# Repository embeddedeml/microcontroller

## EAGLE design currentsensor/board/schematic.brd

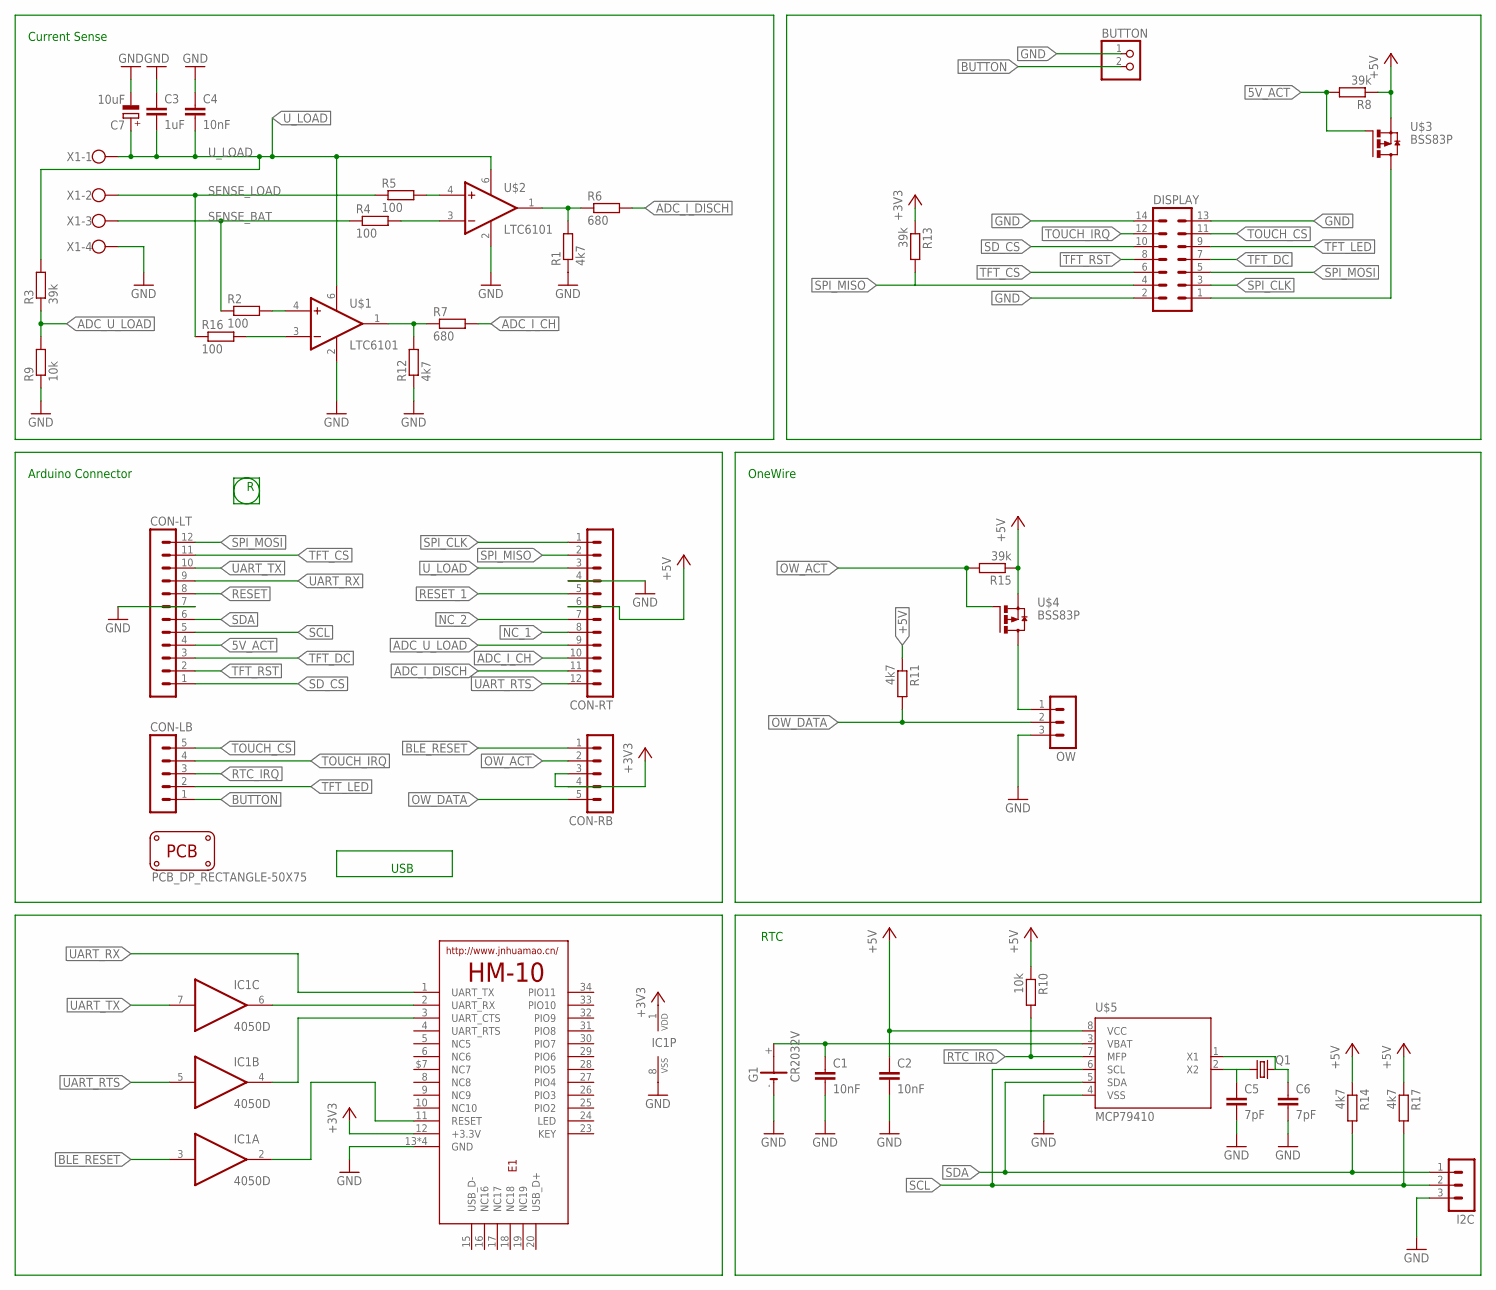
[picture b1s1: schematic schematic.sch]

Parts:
BUTTON: PINHD-1X2; 1X02
C1, C2, C4: 10nF; C1206
C3: 1uF; C1206
C5, C6: 7pF; C1206
C7: 10uF; PANASONIC_B
CON-LB: MA05-1
CON-LT: MA12-1
CON-RB: MA05-1
CON-RT: MA12-1
DISPLAY: MA07-2
E1: HM-10-BOARD; 26.9X13X2.2_BOARD
G1: CR2032V
I2C: MA03-1
IC1: 4050D; SO16
OW: MA03-1
PCB1: PCB_DP_RECTANGLE-50X75; DP5075_V1
Q1: CRYSTALTC26H; TC26H
R1, R11, R12, R14, R17: 4k7; R1206
R2, R4, R5, R16: 100; R1206
R3, R8, R13, R15: 39k; R1206
R6, R7: 680; R1206
R9, R10: 10k; R1206
U$1, U$2: LTC6101; TSOT23-6
U$3, U$4: BSS83P; SOT23
U$5: MCP79410; SOIC8
X1: W237-4

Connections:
5V_ACT: CON-LT.4, R8.2, U$3.1 (G)
+3V3: CON-RB.3, CON-RB.4, E1.12 (+3.3V), IC1.1 (VDD), R13.1
+5V: C2.1, CON-RT.6, R8.1, R10.1, R11.1, R14.1, R15.1, R17.1, U$3.2 (S), U$4.2 (S), U$5.8 (VCC)
ADC_I_CH: CON-RT.10, R7.2
ADC_I_CH_UNPROT: R7.1, R12.2, U$1.1 (OUT1)
ADC_I_DISCH: CON-RT.11, R6.2
ADC_I_DISCH_UNPROT: R1.2, R6.1, U$2.1 (OUT1)
ADC_U_LOAD: CON-RT.9, R3.1, R9.2
BLE_RESET: CON-RB.1, IC1.3 (I)
BUTTON: BUTTON.2, CON-LB.1
GND: BUTTON.1, C1.2, C2.2, C3.1, C4.1, C5.2, C6.2, C7.-, CON-LT.7, CON-RT.4, DISPLAY.2, DISPLAY.13, DISPLAY.14, E1.13 (GND), E1.14 (GND), E1.21 (GND), E1.22 (GND), G1.-, I2C.3, IC1.8 (VSS), OW.3, R1.1, R9.1, R12.1, U$1.2 (V-), U$2.2 (V-), U$5.4 (VSS), X1.4
LCD_5V: DISPLAY.1, U$3.3 (D)
unnamed: R5.2, U$2.4 (+IN)
unnamed: R4.2, U$2.3 (-IN)
unnamed: R2.2, U$1.4 (+IN)
unnamed: R16.2, U$1.3 (-IN)
unnamed: E1.3 (UART_CTS), IC1.4 (O)
unnamed: E1.2 (UART_RX), IC1.6 (O)
unnamed: E1.11 (RESET), IC1.2 (O)
unnamed: OW.1, U$4.3 (D)
unnamed: C5.1, Q1.1, U$5.2 (X2)
unnamed: C6.1, Q1.2, U$5.1 (X1)
NC_1: CON-RT.8
NC_2: CON-RT.7
OW_ACT: CON-RB.2, R15.2, U$4.1 (G)
OW_DATA: CON-RB.5, OW.2, R11.2
RESET: CON-LT.8
RESET_1: CON-RT.5
RTC_IRQ: CON-LB.3, R10.2, U$5.7 (MFP)
SCL: CON-LT.5, I2C.2, R17.2, U$5.6 (SCL)
SDA: CON-LT.6, I2C.1, R14.2, U$5.5 (SDA)
SD_CS: CON-LT.1, DISPLAY.10
SENSE_BAT: R2.1, R4.1, X1.3
SENSE_LOAD: R5.1, R16.1, X1.2
SPI_CLK: CON-RT.1, DISPLAY.3
SPI_MISO: CON-RT.2, DISPLAY.4, R13.2
SPI_MOSI: CON-LT.12, DISPLAY.5
TFT_CS: CON-LT.11, DISPLAY.6
TFT_DC: CON-LT.3, DISPLAY.7
TFT_LED: CON-LB.2, DISPLAY.9
TFT_RST: CON-LT.2, DISPLAY.8
TOUCH_CS: CON-LB.5, DISPLAY.11
TOUCH_IRQ: CON-LB.4, DISPLAY.12
UART_RTS: CON-RT.12, IC1.5 (I)
UART_RX: CON-LT.9, E1.1 (UART_TX)
UART_TX: CON-LT.10, IC1.7 (I)
U_LOAD: C3.2, C4.2, C7.+, CON-RT.3, R3.2, U$1.6 (V+), U$2.6 (V+), X1.1
VBAK: C1.1, G1.+, U$5.3 (VBAT)

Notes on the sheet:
Arduino Connector
Current Sense
USB
OneWire
RTC

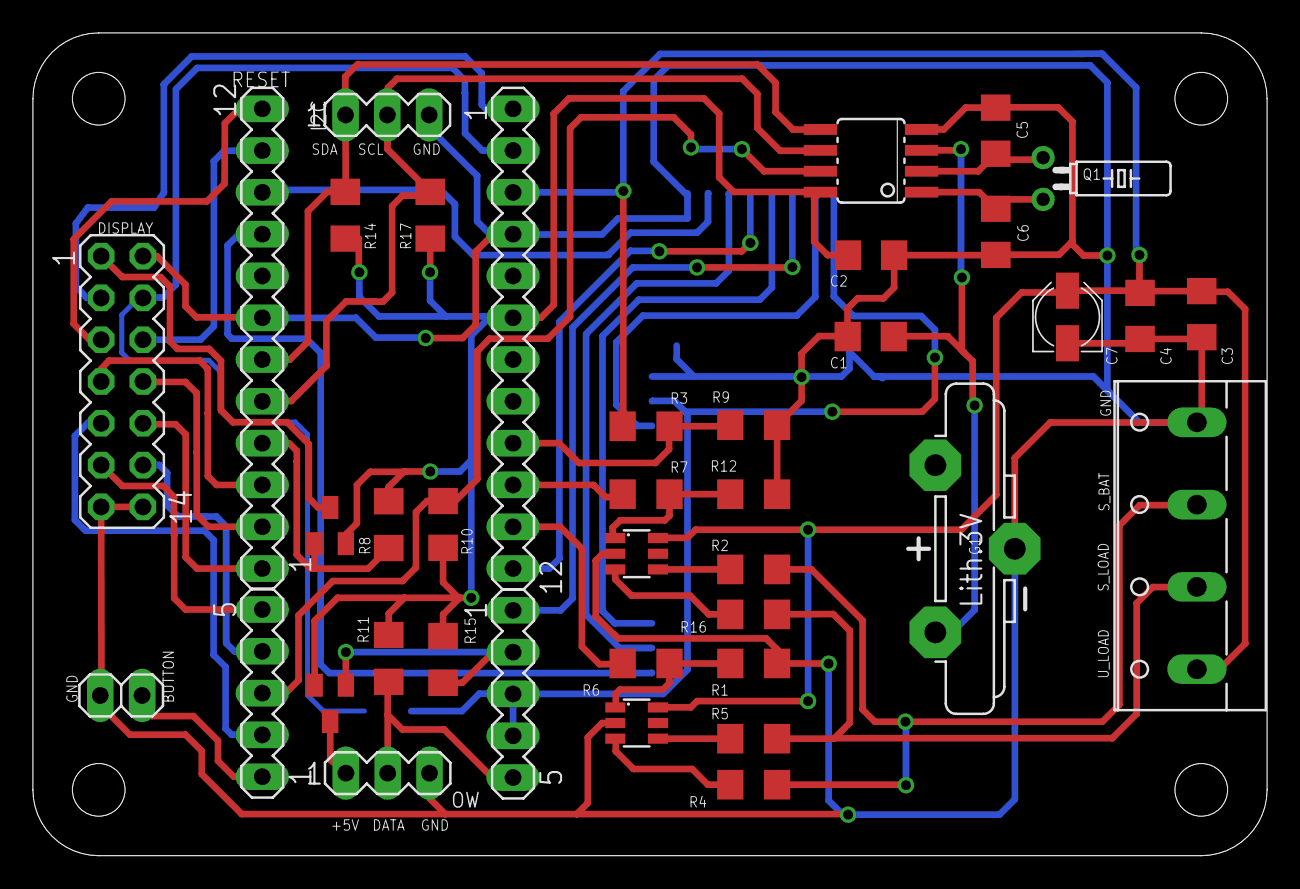
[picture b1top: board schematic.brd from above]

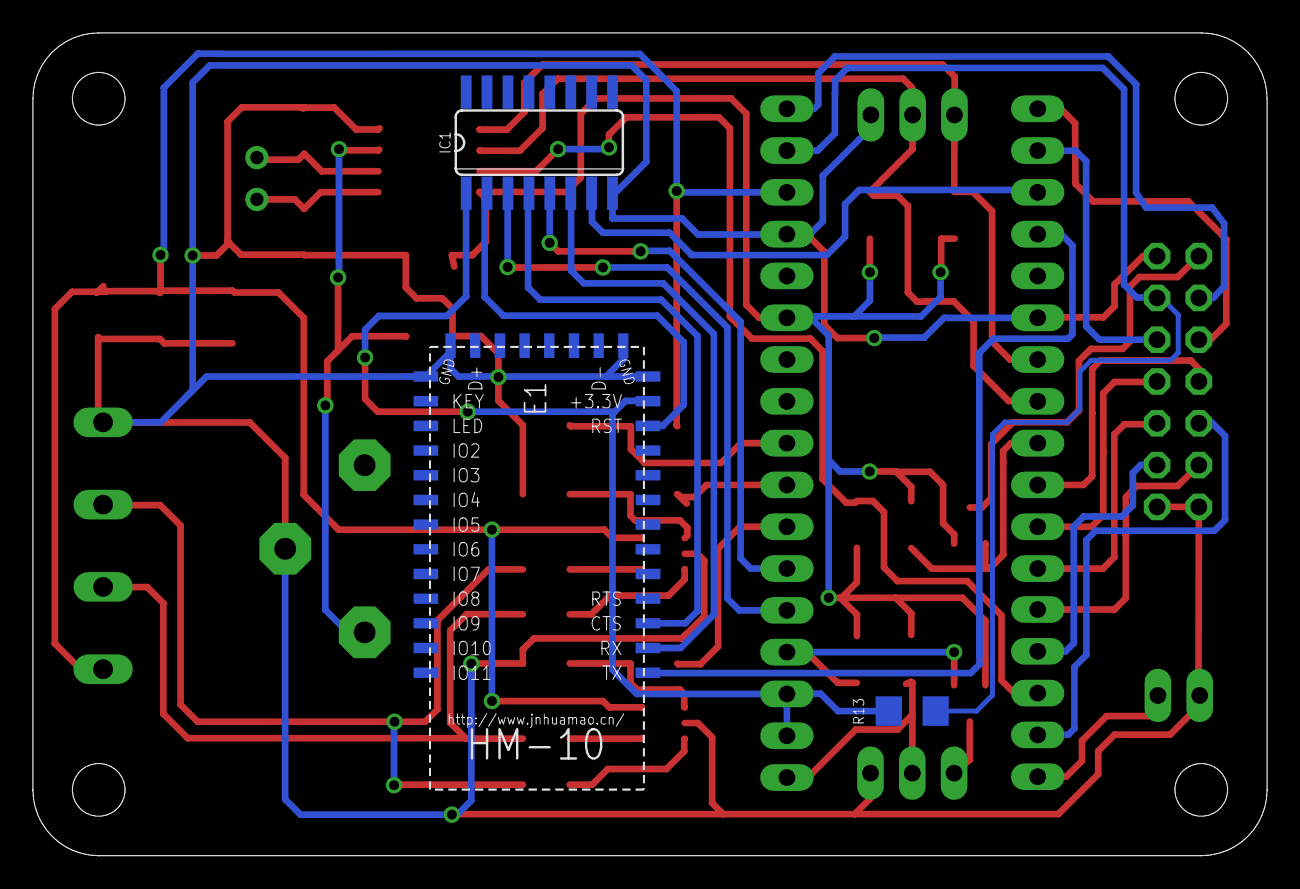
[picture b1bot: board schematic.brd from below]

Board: 2 copper layers, 75.0 x 50.0 mm, 43 parts (3 on the bottom side), 44 nets.

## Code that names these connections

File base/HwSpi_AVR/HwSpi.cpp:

/*
 * Spi.cpp
 *
 *  Created on: Mar 25, 2016
 */

#include "HwSpi.h"
#include "Dio.h"

HwSpi::HwSpi()
{
  pinMode(SPI_CLK,  OUTPUT);
  pinMode(SPI_MOSI, OUTPUT);
  pinMode(SPI_MISO, INPUT);

  /* TODO: set baudrate to fOsc/2 */
  /* SPSR |= (1 << SPI2X); */

  /* enable SPI in master mode */
  SPCR = (1 << SPE) | (1 << MSTR);
}

uint8_t HwSpi::transmitSync(uint8_t c)
{
  /* write data to transmission buffer */
  SPDR = c;

  /* wait for transmission */
  while(!(SPSR & (1<<SPIF)));

  /* return received data */
  return SPDR;
}

HwSpi::~HwSpi()
{

}

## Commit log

2015-02-22 build environment
2015-02-22 build env
2015-02-27 adaption for win
2015-02-27 win support
2015-02-27 doxygen
2015-03-06 win build env
2015-03-06 verification
2015-04-03 return types changed
2015-04-03 Conversion finished indication added
2015-04-03 console support for linux avrdude path changed
2015-04-03 Dem added
2015-04-03 filter added
2015-04-03 HID Support disabled
2015-04-03 new avr version (same as for win)
2015-09-28 optimizations SD lib
2015-10-05 updated to new version
2016-01-19 copterctrl embedded and pc control
2016-01-19 ignore file changed
2016-01-19 pwm module added
2016-01-19 bugfix
2016-01-19 support for additional timer channels
2016-01-19 eagle libs and projects moved to GIT
2016-01-19 layout
2016-01-24 layout finished
2016-01-31 restriction added to gnd plane
2016-02-09 hm-12 added
2016-02-09 restrict area added for hm-10 antenna
2016-02-13 scaling factor corrected
2016-03-26 Touch display driver added
2016-03-26 Boolean type renamed to lower case
2016-03-26 AVR included added
2016-03-26 SPI driver added
2016-03-26 destructor added
2016-03-26 signed int16 type name corrected
2016-03-26 Timer module renamed
2016-03-26 LCD driver added
2016-03-26 SPI double-speed deactivated, since problems with clock generation
2016-03-26 bugfix: missing casting leads to wrong result
2016-03-26 New API for enabling/disabling
2016-03-26 Simple state manager
2016-03-26 Initializing SPI by separate API
2016-03-26 comments changed
2016-03-26 Boundary check added
2016-03-26 eclipse settings changed
2016-03-26 Modules for measurement and display
2016-03-26 UI changed
2016-04-03 RTC driver - draft
